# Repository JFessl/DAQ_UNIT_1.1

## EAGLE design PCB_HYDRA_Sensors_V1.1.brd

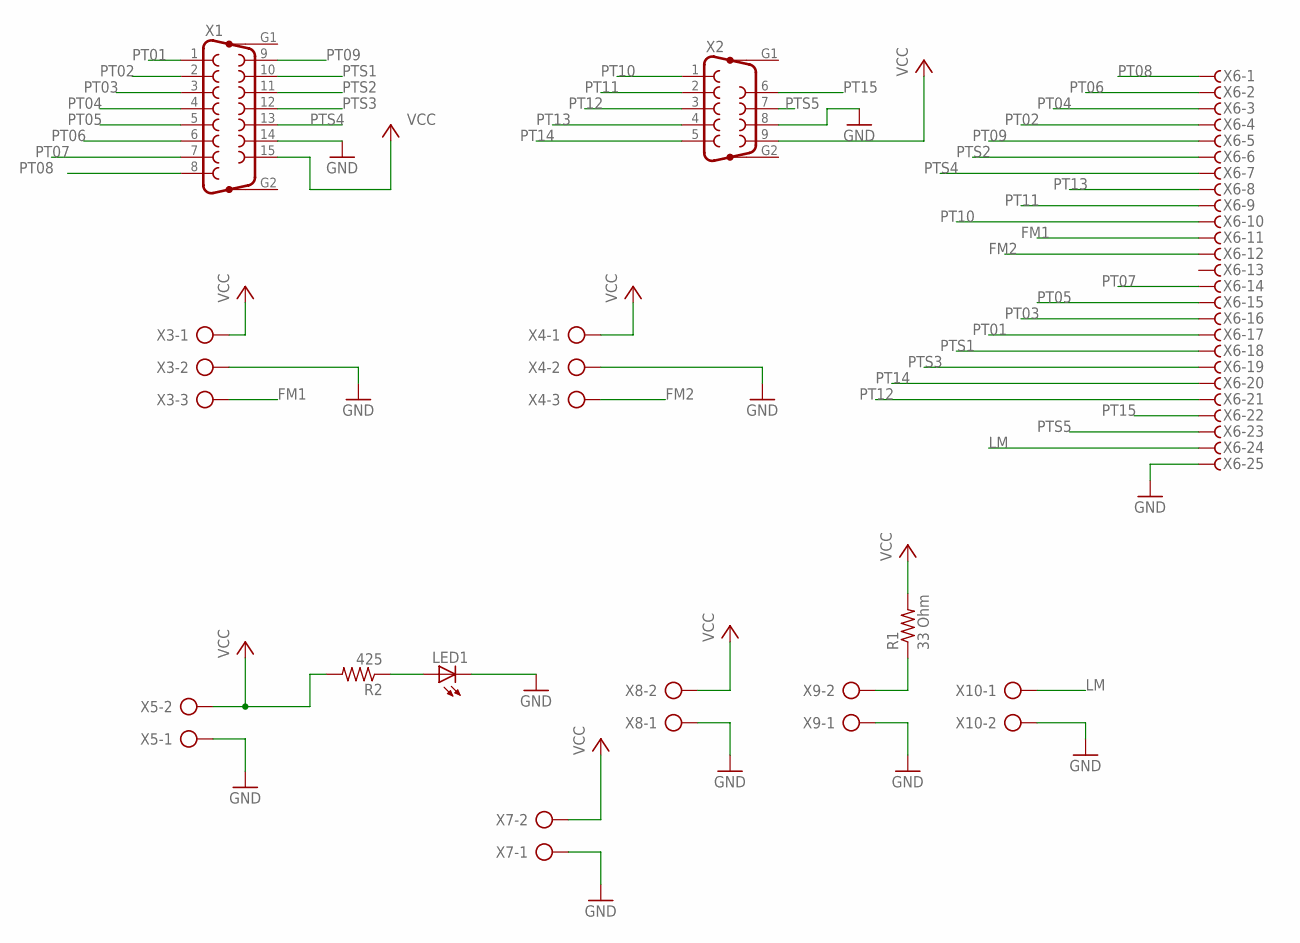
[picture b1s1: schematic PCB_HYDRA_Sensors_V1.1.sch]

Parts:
LED1: LEDCHIPLED_0805; CHIPLED_0805
R1: 33 Ohm; M1206
R2: 425; M1206; MPN M2012ES1G01
X1: F15HP
X2: F09HP
X3, X4: AK300/3
X5, X7, X8, X9, X10: AK300/2
X6: F25HPS; F25HP

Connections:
FM1: X3.3, X6.11
FM2: X4.3, X6.12
GND: LED1.C, X1.14, X2.8, X3.2, X4.2, X5.1, X6.25, X7.1, X8.1, X9.1, X10.2
LM: X6.24, X10.1
unnamed: R1.1, X9.2
unnamed: LED1.A, R2.1
PT01: X1.1, X6.17
PT02: X1.2, X6.4
PT03: X1.3, X6.16
PT04: X1.4, X6.3
PT05: X1.5, X6.15
PT06: X1.6, X6.2
PT07: X1.7, X6.14
PT08: X1.8, X6.1
PT09: X1.9, X6.5
PT10: X2.1, X6.10
PT11: X2.2, X6.9
PT12: X2.3, X6.21
PT13: X2.4, X6.8
PT14: X2.5, X6.20
PT15: X2.6, X6.22
PTS1: X1.10, X6.18
PTS2: X1.11, X6.6
PTS3: X1.12, X6.19
PTS4: X1.13, X6.7
PTS5: X2.7, X6.23
VCC9: R1.2, R2.2, X1.15, X2.9, X3.1, X4.1, X5.2, X7.2, X8.2

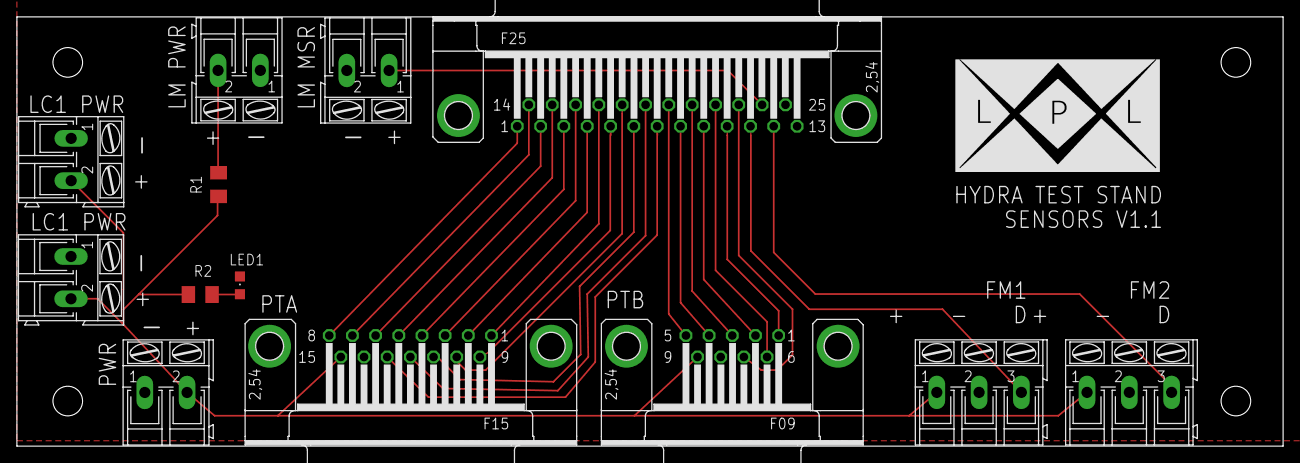
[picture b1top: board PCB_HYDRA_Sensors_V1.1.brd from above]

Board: 2 copper layers, 149.9 x 50.8 mm, 13 parts (0 on the bottom side), 27 nets.

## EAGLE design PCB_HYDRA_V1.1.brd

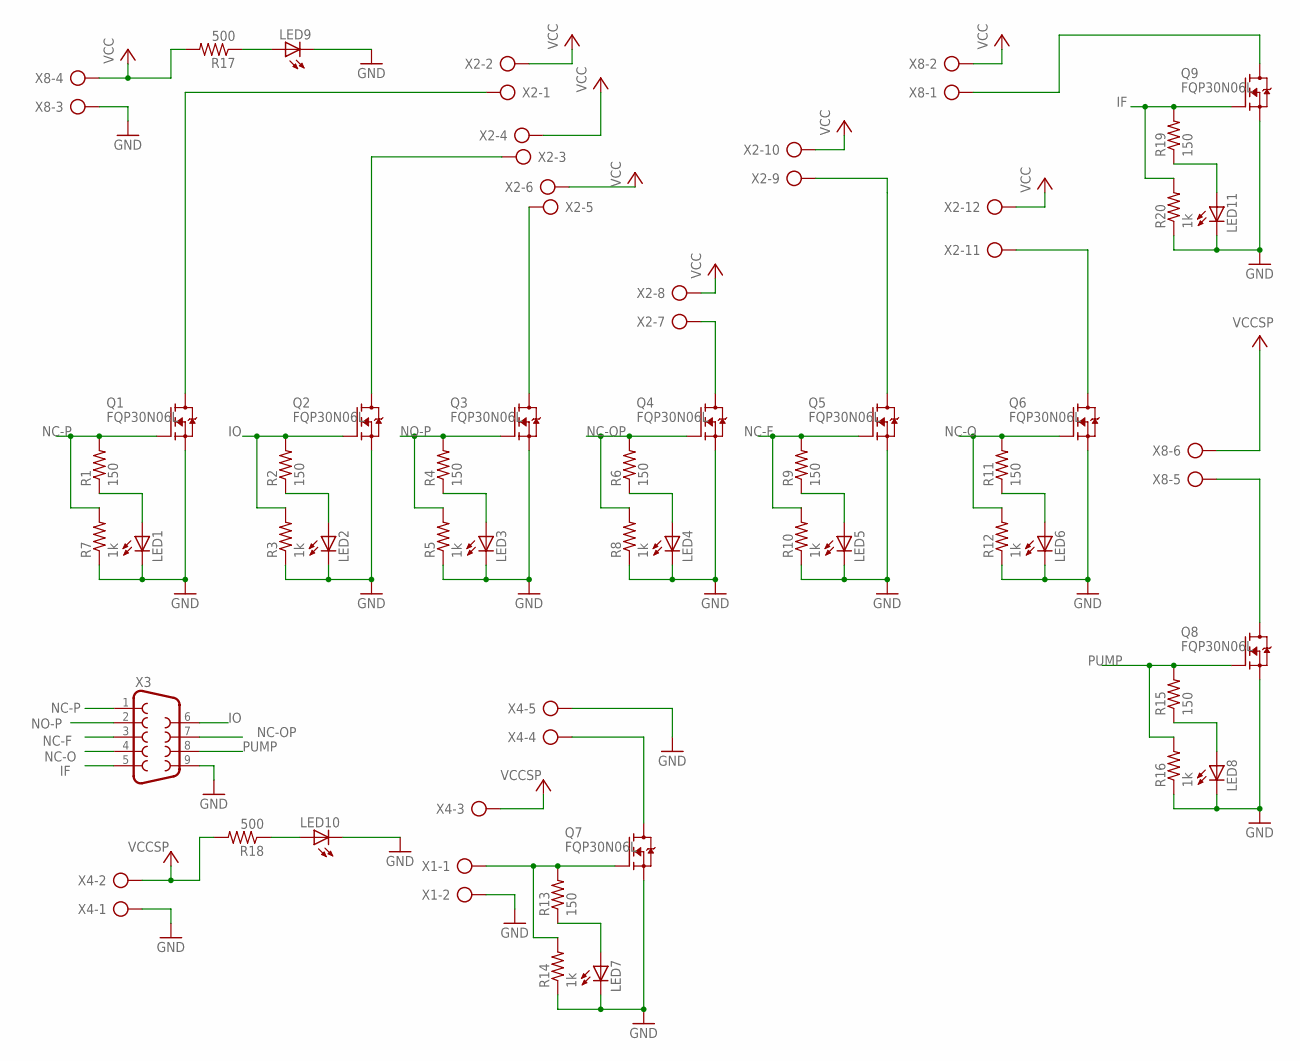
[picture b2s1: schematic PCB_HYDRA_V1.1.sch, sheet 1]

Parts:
LED1, LED2, LED3, LED4, LED5, LED6, LED7, LED8, LED9, LED10, LED11: LEDCHIPLED_0805; CHIPLED_0805
Q1, Q2, Q3, Q4, Q5, Q6, Q7, Q8, Q9: FQP30N06L; TO220V; MPN STP36NF06L
R1, R2, R4, R6, R9, R11, R13, R15, R19: 150; M1206; MPN M2012ES1G01
R3, R5, R7, R8, R10, R12, R14, R16, R20: 1k; M1206; MPN M2012ES1G01
R17, R18: 500; M1206; MPN M2012ES1G01
X1: AK300/2
X2: AK300/12
X3: F09H
X4: AK300/5
X8: AK300/6

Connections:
GND: LED1.C, LED2.C, LED3.C, LED4.C, LED5.C, LED6.C, LED7.C, LED8.C, LED9.C, LED10.C, LED11.C, Q1.3 (S), Q2.3 (S), Q3.3 (S), Q4.3 (S), Q5.3 (S), Q6.3 (S), Q7.3 (S), Q8.3 (S), Q9.3 (S), R3.1, R5.1, R7.1, R8.1, R10.1, R12.1, R14.1, R16.1, R20.1, X1.2, X3.9, X4.1, X4.5, X8.3; also elsewhere on the board
IF: Q9.1 (G), R19.2, R20.2, X3.5
IO: Q2.1 (G), R2.2, R3.2, X3.6
unnamed: Q1.2 (D), X2.1
unnamed: Q2.2 (D), X2.3
unnamed: Q3.2 (D), X2.5
unnamed: Q4.2 (D), X2.7
unnamed: Q5.2 (D), X2.9
unnamed: Q6.2 (D), X2.11
unnamed: LED7.A, R13.1
unnamed: LED1.A, R1.1
unnamed: LED8.A, R15.1
unnamed: LED2.A, R2.1
unnamed: Q7.2 (D), X4.4
unnamed: LED3.A, R4.1
unnamed: LED4.A, R6.1
unnamed: Q8.2 (D), X8.5
unnamed: LED5.A, R9.1
unnamed: LED9.A, R17.1
unnamed: LED6.A, R11.1
unnamed: LED10.A, R18.1
unnamed: LED11.A, R19.1
unnamed: Q9.2 (D), X8.1
NC-F: Q5.1 (G), R9.2, R10.2, X3.3
NC-O: Q6.1 (G), R11.2, R12.2, X3.4
NC-OP: Q4.1 (G), R6.2, R8.2, X3.7
NC-P: Q1.1 (G), R1.2, R7.2, X3.1
NO-P: Q3.1 (G), R4.2, R5.2, X3.2
PUMP: Q8.1 (G), R15.2, R16.2, X3.8
SIGNAL: Q7.1 (G), R13.2, R14.2, X1.1
VCC: R17.2, X2.2, X2.4, X2.6, X2.8, X2.10, X2.12, X8.2, X8.4
VCCSP: R18.2, X4.2, X4.3, X8.6

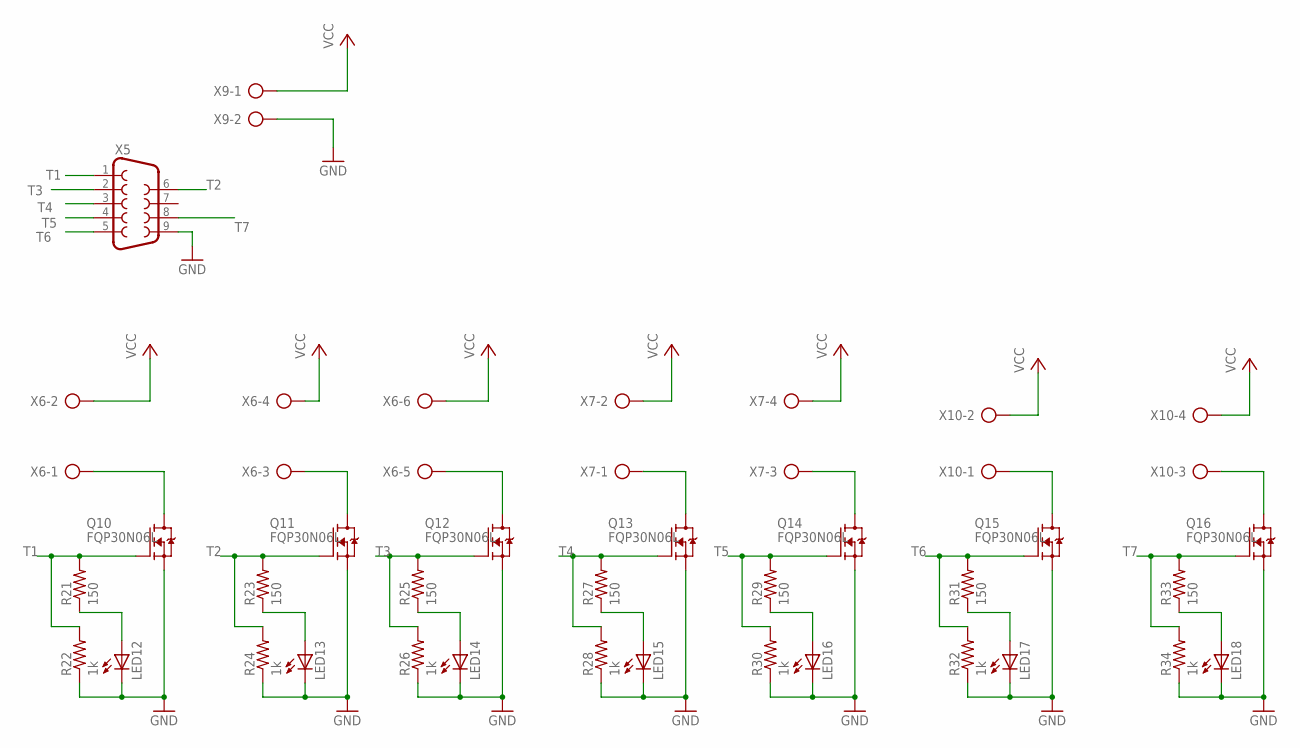
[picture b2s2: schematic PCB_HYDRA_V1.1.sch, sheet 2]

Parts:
LED12, LED13, LED14, LED15, LED16, LED17, LED18: LEDCHIPLED_0805; CHIPLED_0805
Q10, Q11, Q12, Q13, Q14, Q15, Q16: FQP30N06L; TO220V; MPN STP36NF06L
R21, R23, R25, R27, R29, R31, R33: 150; M1206; MPN M2012ES1G01
R22, R24, R26, R28, R30, R32, R34: 1k; M1206; MPN M2012ES1G01
X5: F09H
X6: AK300/6
X7, X10: AK300/4
X9: AK300/2

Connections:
GND: LED12.C, LED13.C, LED14.C, LED15.C, LED16.C, LED17.C, LED18.C, Q10.3 (S), Q11.3 (S), Q12.3 (S), Q13.3 (S), Q14.3 (S), Q15.3 (S), Q16.3 (S), R22.1, R24.1, R26.1, R28.1, R30.1, R32.1, R34.1, X5.9, X9.2; also elsewhere on the board
unnamed: LED12.A, R21.1
unnamed: LED13.A, R23.1
unnamed: LED14.A, R25.1
unnamed: LED15.A, R27.1
unnamed: LED16.A, R29.1
unnamed: LED17.A, R31.1
unnamed: LED18.A, R33.1
unnamed: Q10.2 (D), X6.1
unnamed: Q11.2 (D), X6.3
unnamed: Q12.2 (D), X6.5
unnamed: Q13.2 (D), X7.1
unnamed: Q15.2 (D), X10.1
unnamed: Q14.2 (D), X7.3
unnamed: Q16.2 (D), X10.3
T1: Q10.1 (G), R21.2, R22.2, X5.1
T2: Q11.1 (G), R23.2, R24.2, X5.6
T3: Q12.1 (G), R25.2, R26.2, X5.2
T4: Q13.1 (G), R27.2, R28.2, X5.3
T5: Q14.1 (G), R29.2, R30.2, X5.4
T6: Q15.1 (G), R31.2, R32.2, X5.5
T7: Q16.1 (G), R33.2, R34.2, X5.8
VCCS: X6.2, X6.4, X6.6, X7.2, X7.4, X9.1, X10.2, X10.4

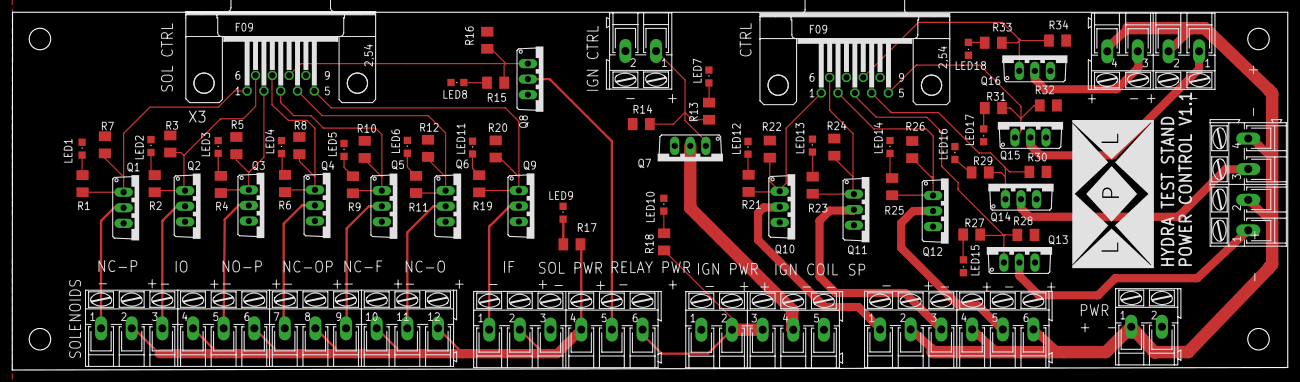
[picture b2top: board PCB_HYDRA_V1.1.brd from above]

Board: 2 copper layers, 208.3 x 58.4 mm, 78 parts (0 on the bottom side), 54 nets.

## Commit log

2019-03-20 Add files via upload
    This PCB is including 16 MOSFET switches to control valves in a high-pressure system and high power pump.
2019-03-20 Manufacturing Files
2019-03-20 Board Layout
    PCB design with 16 MOSFET switches to actuate valves in a high-pressure system and high power pump.
2019-03-20 Schematics
    PCB design with 16 MOSFET switches to actuate valves in a high-pressure system and high power pump.
2019-03-20 Manufacturing Files
    PCB design serving as an interface between NI DAQ hardware and sensors. PCB is providing power distribution to all sensors.
2019-03-20 Board Layout
    PCB design serving as an interface between NI DAQ hardware and sensors. PCB is providing power distribution to all sensors.
2019-03-20 Schematics
    PCB design serving as an interface between NI DAQ hardware and sensors. PCB is providing power distribution to all sensors.
